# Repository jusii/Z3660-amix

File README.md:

# Z3660 by sHaNsHe (Double H Tech)

<!-- fork:amix begin — self-contained fork section, safe to drop on an upstream merge -->
> ## This fork — Amiga UNIX (AMIX) support
>
> This is an **Amix-interoperability fork** of [shanshe/Z3660](https://github.com/shanshe/Z3660)
> (GPL-3.0, full credit to sHaNsHe). It adds a **real 68030 PMMU emulator** and an **emulated
> A3000 mainboard SCSI** so a Z3660 + Z-turn can boot **Amiga UNIX (AMIX) 2.1**. If you don't run
> AMIX, nothing changes — the additions default to off and upstream behaviour is unchanged.
>
> **What's new in this fork** (full reference: **[docs/AMIX.md](docs/AMIX.md)**):
> - **68030 PMMU emulation** — new `bootmode UAE_030_MMU` (a 68030 interpreter *with* a working PMMU).
> - **Emulated A3000 SCSI** — AMIX's kernel bootstrap path (SuperDMAC + WD33C93).
> - **New config knobs** — `amix_mode` (AMIX memory contract) and `service_cadence` (emulator
>   throughput vs. interrupt latency), plus `DEMU`/`DSCSI` runtime debug gating and the
>   `perf_stats`/`emu_probes`/`core0_stats` run-loop overhead switches (all default to the
>   unchanged behaviour).
> - **Guest-side AMIX drivers** — the SCSI and ethernet drivers that run *inside* AMIX against the
>   protocol this firmware serves have their own repos:
>   **[amix-z3660scsi](https://github.com/jusii/amix-z3660scsi)** and
>   **[amix-z3660net](https://github.com/jusii/amix-z3660net)**. The kernel that carries them is
>   assembled with the shared build harness in
>   **[amix-kerntools](https://github.com/jusii/amix-kerntools)**.
>
> ### Quick start — try a pre-built firmware
> 1. Download `BOOT.BIN` from this repo's **Releases** (no build needed), or build it yourself —
>    see *Build it yourself* below.
> 2. Copy it to the SD card's FAT32 boot partition; use the layout in
>    [`z3660-zturn_SD_content/`](z3660-zturn_SD_content/) for the rest.
> 3. **You supply your own Kickstart ROM(s) and disk image** — Amiga OS ROMs and AMIX itself are
>    copyrighted and are not included.
>
> ### Build it yourself
> A dockerised toolchain builds the firmware and the Amiga-side drivers — see
> **[docker/README.md](docker/README.md)**. (Drivers build with no AMD account; the full firmware
> build needs you to download AMD/Xilinx Vitis 2023.2 yourself — it is staged outside the repo and
> never committed.)
>
> Three firmware images come out of the one tree. `make bootbin` gives the usual **`BOOT.BIN`**,
> with the emulator's run-loop diagnostics compiled in and switchable at runtime; `make lean` gives
> **`BOOT-lean.BIN`**, the production image with those diagnostics — and their per-instruction
> predicates — compiled out; and `make profile` gives **`BOOT-prof.BIN`**, the lean image plus an
> interpreter profiler (a wall-clock guest-PC sampler and per-stage ARM cycle attribution). The
> profiling image is a measuring instrument, not a production one — it costs measured time to run.
> Every build also drops a CRC-stamped copy of its image, plus the matching core1 emulator ELF,
> in `sd_card/archive/` (untracked), so a rebuild never destroys the image you are comparing
> against, and a flown image's disassembly stays readable after the build directory has moved on.
> Details in
> **[docs/AMIX.md](docs/AMIX.md)** and **[docs/profiler.md](docs/profiler.md)**.
>
> A fourth target, `make q2probe`, builds **`BOOT-q2probe.BIN`** — a throwaway experiment image
> that answers one open design question about generated code and prints its verdict on serial
> before emulation starts. It is compiled out of all three images above (their CRCs are
> unchanged whether it exists in the tree or not), and it is meant to be booted once, not left
> on a card. See **[docs/WARP-ENGINE.md](docs/WARP-ENGINE.md)**.
>
> ### Running AMIX
> Needs an **A3000-variant Kickstart** (A4000 ROMs can't boot AMIX) and an **AMIX disk image** placed
> on the **SCSI id it was installed on** (id 6 for the usual A3000 install — see the note in
> docs/AMIX.md). AMIX 2.1 **boots to a stable multiuser login shell**; full setup, the SCSI-id rule
> and current status are in **[docs/AMIX.md](docs/AMIX.md)**.
>
> ### Branches
> - **`amix-main-2` — the branch of record.** The Amix work rebuilt on upstream firmware
>   **v1.03 beta 21**. Upstream rewrote its history, so there was no merge base and the resync had
>   to be a guided replay rather than a merge;
>   **[docs/port-ledger-beta21.md](docs/port-ledger-beta21.md)** is the analysis behind it.
> - **`amix-main`** — the superseded pre-beta-21 line, kept for reference. It shares no ancestry
>   with `amix-main-2`. Documents dated before the resync describe that tree and say so.
>
> ### The fork's own documents
> - **[docs/AMIX.md](docs/AMIX.md)** — the AMIX reference: boot modes, the new config keys, how the
>   A3000-SCSI bootstrap works, current status, and the upstream defects this resync turned up.
> - **[KNOWN_ISSUES.md](KNOWN_ISSUES.md)** — limitations, including the fork note on the real-CPU
>   `cpufreq` ceiling being a per-card property.
> - **[CHANGELOG.md](CHANGELOG.md)** — this fork's history and its measurements. (Upstream's own
>   history is the separate **CHANGES.md**, which the text below points you at.)
> - **[docs/](docs/)** — the engineering references: clock timings, the piscsi service path, the
>   HTTP/TFTP deploy route, the WARP decoded-op-cache engine, the interpreter profiler.
<!-- fork:amix end -->

<br>Z3660 is an Amiga 4000 CPU accelerator board based on A3660 and Z-turn FPGA board.
<br>
<br>Compared to A3660, Z3660 has some key differences:
<br><p style="margin-left:1em;">
<br><b>1</b>. Z3660 accelerator board can only use 060 CPUs. This could be changed in the future, but at this time, only 060 is supported.
<br>
<br><b>2</b>. If Z-turn FPGA board is <b>NOT</b> used, then you get a simple A3660. The only difference is that all A3660 PLDs are replaced by a XC95144XL-10TQ144 CPLD. It could be possible to use 060 up to 100MHz, but only 50 MHz and 64 MHz has been tested. A board with 128 MB of CPU RAM is in the works (to be connected at Z-turn sockets).
<br>
<br><b>3</b>. If you <b>use a Z-turn FPGA board</b>, then you can add 128 MB of CPU RAM (DMA compatible), 256 MB of Z3 RAM (not DMA compatible), RTG 16bit, Ethernet, AHI and MHI. Also there is a SD to SCSI emulation for using raw RDB disk images (USB storage maybe in the future). And of course, you can use a 68060 rev6 at 100 MHz.
<br><p style="margin-left:0em;">
<br><b>Main branch. Z3660 with Z-turn FPGA</b>
<br>
<br>This main branch has everything you need to build a Z3660 with Z-turn FPGA.
<br>If you want to build Z3660 without Z-turn FPGA, please go to wo_FPGA branch. The board is the same, but the CPLD firmware and BOM are obviously different.
<br>
<br>Current version of Schematics is v021. It has all fixes needed by v02 to have DMA compatibility (tested with ReA4091 as bus master), so you can build it.
<br>
<br>The exact model of Z-Turn board you will need is: MYS-7Z020-V2 ( [mouser](https://www.mouser.com/c/?q=MYS-7Z020-V2-0E1D-766-C) (C or C-S. C-S has restrictions on EU - UK) ).

<br>
<br><p style="text-align:center;"><br>v0.2 Z3660 without FPGA</br></p>
<br>
<br><p style="text-align:center;"><br>v0.2 Z3660 with FPGA</br></p>
In this version you can see that I have used a 3V3 DCDC converter, instead of old linear regulator on VR1. Board has both footprints in one. Please be careful with its connection.
<br>
<br>Note on RTG status: RTG is full working now. It has all features that ZZ9000 has (except obviously scandoubler). Due limitations of Z-turn, output video is limited to 16 bit.
<br>Manufacturer ID was asigned to 5195 decimal, 0x144B hexadecimal (thanks to Olaf Barthel).
<br>All RTG, AHI and MHI are based on [ZZ9000 RTG](https://source.mnt.re/explore).
It has the same band-pass filters as the AX module, but made in software by one of the ARMs.
<br>
<br><b>And finally, a checkmate move...</b>
<br>
<br><i>Don't have a 060 rev6 CPU, and still want to try Z3660 with a Z-turn?</i>
<br><i>sHaNsHe to the rescue!!! :P</i>
<br>
<br>One of the Z-turn ARM CPU can run the emulation code of a 68040 CPU with JIT that reaches up to 120 MIPS!!!<br>It is based on Amiberry CPU code (for 32bit ARM). (And yes, I know, but Emu68 no longer supports 32 bit ARM).
<br>You can even switch between the real 060 CPU and the emulation by clicking on an app (and rebooting).
<br>
<br><b>Discord channel link:</b>
<br><br>https://discord.gg/ua4u6SzyHf
<br>
<br><b>Documents to read before using your Z3660</b><br>
<br> You should read the "KNOWN_ISSUES.md" and "CHANGES.md" files to know the latest news.
<br> Thanks to ByteMavericks we have now the [wiki](https://github.com/shanshe/Z3660/wiki)

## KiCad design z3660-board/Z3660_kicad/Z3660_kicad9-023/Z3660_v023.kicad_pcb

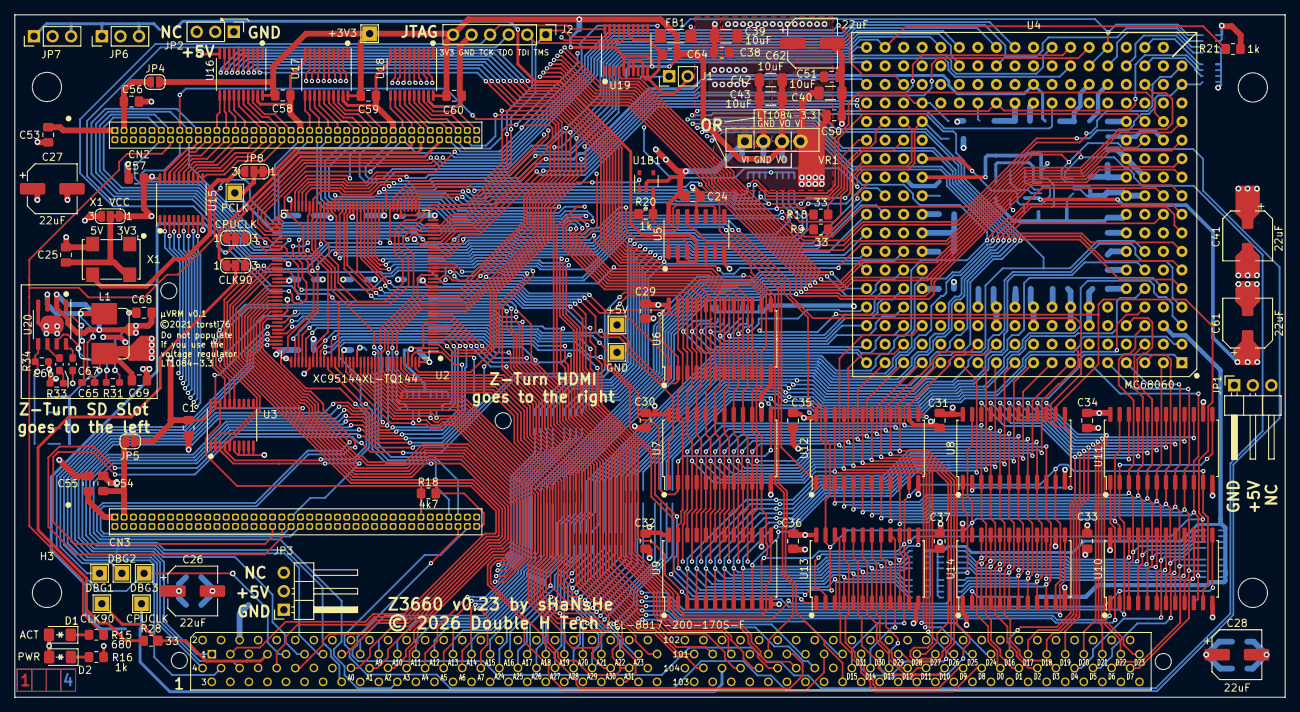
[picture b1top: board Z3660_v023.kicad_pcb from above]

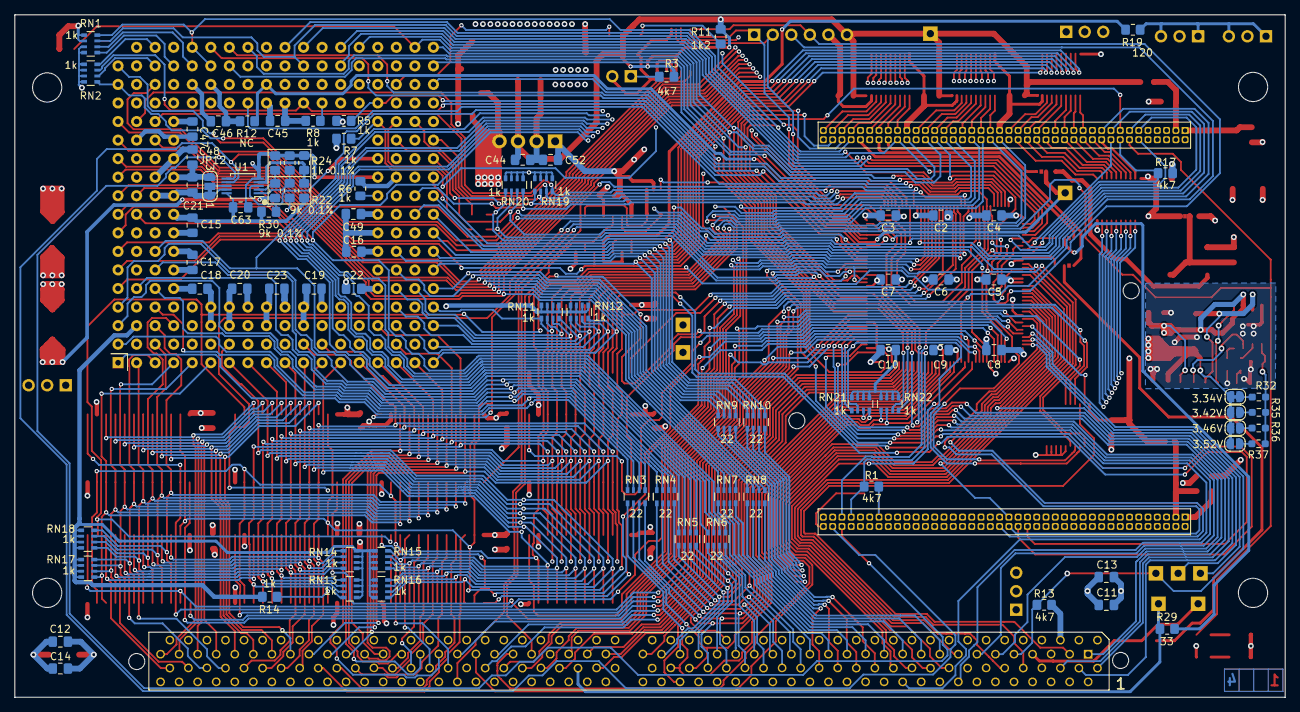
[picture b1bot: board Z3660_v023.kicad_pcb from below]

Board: 4 copper layers, 173.9 x 93.4 mm, 195 parts (87 on the bottom side), 321 nets.

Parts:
C1, C2, C3, C4, C5, C6, C7, C8, C9, C10, C11, C12, C13, C14, C15, C16, C17, C18, C19, C20, C21, C22, C23, C24, C25, C29, C30, C31, C32, C33, C34, C35, C36, C37, C38, C44, C45, C46, C47, C48, C49, C50, C51, C52, C53, C54, C55, C56, C57, C58, C59, C60, C63, C64: 100nF; C_0805_2012Metric_Pad1.18x1.45mm_HandSolder
C26, C28, C41, C61, C62: 22uF; CP_Elec_6.3x5.4
C27: 22uF; CP_Elec_6.3x3.9
C39, C40, C42, C43: 10uF; C_1206_3216Metric_Pad1.33x1.80mm_HandSolder
C65: 10nF; C_0603_1608Metric_Pad1.08x0.95mm_HandSolder
C66: 3.9nF; C_0603_1608Metric_Pad1.08x0.95mm_HandSolder
C67: 100nF; C_0603_1608Metric_Pad1.08x0.95mm_HandSolder
C68: 10uF; C_0805_2012Metric_Pad1.18x1.45mm_HandSolder
C69: 22uF; C_0805_2012Metric_Pad1.18x1.45mm_HandSolder
CN1: KEL-8817-200-170S-F; xIP-200
CN2: Conn_02x40_Odd_Even; PinHeader_2x40_P1.27mm_Vertical
CN3: Conn_02x40_Odd_Even; PinHeader_2x40_P1.27mm_Vertical_CN3
D1: LED_Small_Green; LED_1206_3216Metric_Pad1.42x1.75mm_HandSolder
D2: LED_Small_Red; LED_1206_3216Metric_Pad1.42x1.75mm_HandSolder
DBG1, DBG2, DBG3: PCLK; TestPoint_THTPad_2.0x2.0mm_Drill1.0mm
FB1: Ferrite_Bead_Small; Fuse_1806_4516Metric_Pad1.57x1.80mm_HandSolder
H1, H2, H3, H4: MountingHole; MountingHole_4mm
H5, H6, H7, H8: MountingHole; MountingHole_2.2mm_M2
J1: Jumper_2_Open; PinHeader_1x02_P2.54mm_Vertical
J2: JTAG; PinHeader_1x06_P2.54mm_Vertical
JP1, JP3: Jumper_NO_Small; PinHeader_1x03_P2.54mm_Horizontal
JP2, JP6, JP7: Jumper_3_Open; PinHeader_1x03_P2.54mm_Vertical
JP4, JP5: BRIDGE_3V3; SolderJumper-2_P1.3mm_Open_RoundedPad1.0x1.5mm
JP8, JP9, JP10, JP11, JP12: SolderJumper_3_Bridged12; SolderJumper-3_P1.3mm_Bridged12_RoundedPad1.0x1.5mm_NumberL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
JP13, JP14, JP15, JP16: SolderJumper_2_Open; small_SolderJumper-2_P1.3mm_Open_RoundedPad1.0x1.5mm
L1: 10uH; L_Bourns_SRP7028A_7.3x6.6mm
NT1, NT2, NT3, NT4: NetTie_2; NetTie-2_SMD_Pad0.5mm
R1, R3, R13, R17, R18: 4k7; R_0805_2012Metric_Pad1.20x1.40mm_HandSolder
R5, R6, R7, R8, R14, R16, R20, R21: 1k; R_0805_2012Metric_Pad1.20x1.40mm_HandSolder
R9, R10, R28, R29: 33; R_0805_2012Metric_Pad1.20x1.40mm_HandSolder
R11: 1k2; R_0805_2012Metric_Pad1.20x1.40mm_HandSolder
R12: NC; R_0805_2012Metric_Pad1.20x1.40mm_HandSolder
R15: 680; R_0805_2012Metric_Pad1.20x1.40mm_HandSolder
R19: 120; R_0805_2012Metric_Pad1.20x1.40mm_HandSolder
R22, R26, R27, R30: 9k 0.1%; R_0805_2012Metric_Pad1.20x1.40mm_HandSolder
R23, R24, R25: 1k 0.1%; R_0805_2012Metric_Pad1.20x1.40mm_HandSolder
R31: 100k; R_0603_1608Metric_Pad0.98x0.95mm_HandSolder
R32: 26.1k*; R_0603_1608Metric_Pad0.98x0.95mm_HandSolder
R33: 6.8k; R_0603_1608Metric_Pad0.98x0.95mm_HandSolder
R34: 10k; R_0603_1608Metric_Pad0.98x0.95mm_HandSolder
R35: 27.0k; R_0603_1608Metric_Pad0.98x0.95mm_HandSolder
R36: 27.4k; R_0603_1608Metric_Pad0.98x0.95mm_HandSolder
R37: 28.0k; R_0603_1608Metric_Pad0.98x0.95mm_HandSolder
RN1, RN2, RN11, RN12, RN13, RN14, RN15, RN16, RN17, RN18, RN19, RN20, RN21, RN22: 1k; R_Array_Convex_4x0603
RN3, RN4, RN5, RN6, RN7, RN8, RN9, RN10: 22; R_Array_Convex_4x0603
TP1: +3V3; TestPoint_THTPad_2.0x2.0mm_Drill1.0mm
TP4: +5V; TestPoint_THTPad_2.0x2.0mm_Drill1.0mm
TP8: GND; TestPoint_THTPad_2.0x2.0mm_Drill1.0mm
TP9: PCLK; TestPoint_THTPad_2.0x2.0mm_Drill1.0mm
TP10: CLK90; TestPoint_THTPad_2.0x2.0mm_Drill1.0mm
TP11: CPUCLK; TestPoint_THTPad_2.0x2.0mm_Drill1.0mm
U1: LTC2990; MSOP-10_3x3mm_P0.5mm
U1B1: BU4942; TSOP-5_1.65x3.05mm_P0.95mm
U2: XC95144XL-TQ144; TQFP-144_20x20mm_P0.5mm
U3, U15, U16, U17, U18: SN74CB3T3245PW; TSSOP-20_4.4x6.5mm_P0.65mm
U4: MC68060; PGA226
U5: 7407; SOIC-14_3.9x8.7mm_P1.27mm
U6, U7, U8, U9, U10, U11, U12, U13, U14: 74FCT543A; SOIC-24W_7.5x15.4mm_P1.27mm
U19: PCF8574TS; TSSOP-20_4.4x6.5mm_P0.65mm
U20: MP2307; SOIC-8-1EP_3.9x4.9mm_P1.27mm_EP2.514x3.2mm
VR1: LT1084-3.3_EXTENDED; Regulador_DCDC
X1: IQXO-70; Oscillator_SMD_IQD_IQXO70-4Pin_7.5x5.0mm

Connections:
3.3V_ZTURN1: C54.1, CN3.3, JP5.1 (A)
3.3V_ZTURN2: C56.1, CN2.3, JP4.1 (A)
040A0: RN10.4 (R4.1), RN22.6 (R3.2), U2.121
040A1: RN10.3 (R3.1), RN22.5 (R4.2), U2.124
040A2: RN10.2 (R2.1), RN21.8 (R1.2), U2.125
040A3: RN10.1 (R1.1), RN21.7 (R2.2), U2.126
040A4: CN1.52 (A4), RN9.4 (R4.1)
040A5: CN1.56 (A5), RN9.3 (R3.1)
040A6: CN1.60 (A6), RN9.2 (R2.1)
040A7: CN1.64 (A7), RN9.1 (R1.1)
040A8: CN1.33 (A8), RN8.4 (R4.1)
040A9: CN1.37 (A9), RN8.3 (R3.1)
040A10: CN1.41 (A10), RN8.2 (R2.1)
040A11: CN1.45 (A11), RN8.1 (R1.1)
040A12: CN1.49 (A12), RN7.4 (R4.1)
040A13: CN1.53 (A13), RN7.3 (R3.1)
040A14: CN1.57 (A14), RN7.2 (R2.1)
040A15: CN1.61 (A15), RN7.1 (R1.1)
040A16: CN1.65 (A16), RN6.4 (R4.1)
040A17: CN1.69 (A17), RN6.3 (R3.1)
040A18: CN1.73 (A18), RN6.2 (R2.1)
040A19: CN1.77 (A19), RN6.1 (R1.1), U2.140
040A20: CN1.81 (A20), RN5.4 (R4.1), U2.139
040A21: CN1.85 (A21), RN5.3 (R3.1), U2.138
040A22: CN1.89 (A22), RN5.2 (R2.1), U2.137
040A23: CN1.93 (A23), RN5.1 (R1.1), U2.136
040A24: CN1.68 (MA24), RN4.4 (R4.1), U2.135
040A25: CN1.72 (MA25), RN4.3 (R3.1), U2.134
040A26: CN1.76 (MA26), RN4.2 (R2.1), U2.133
040A27: CN1.80 (A27), RN4.1 (R1.1), U2.132
040A28: CN1.84 (A28), RN3.4 (R4.1), U2.131
040A29: CN1.88 (A29), RN3.3 (R3.1), U2.130
040A30: CN1.92 (A30), RN3.2 (R2.1), U2.129
040A31: CN1.96 (A31), RN3.1 (R1.1), U2.128
060A0: RN10.5 (R4.2), U4.102 (A0), U16.9 (A7)
060A1: RN10.6 (R3.2), U4.96 (A1), U16.8 (A6)
060A2: RN10.7 (R2.2), U4.89 (A2), U16.7 (A5)
060A3: RN10.8 (R1.2), U4.90 (A3), U16.6 (A4)
060A4: RN9.5 (R4.2), U4.84 (A4), U16.5 (A3)
060A5: RN9.6 (R3.2), U4.78 (A5), U16.4 (A2)
060A6: RN9.7 (R2.2), U4.76 (A6), U16.3 (A1)
060A7: RN9.8 (R1.2), U4.72 (A7), U16.2 (A0)
060A8: RN8.5 (R4.2), U4.66 (A8), U17.9 (A7)
060A9: RN8.6 (R3.2), U4.70 (A9), U17.8 (A6)
060A10: RN8.7 (R2.2), U4.115 (A10), U17.7 (A5)
060A11: RN8.8 (R1.2), U4.111 (A11), U17.6 (A4)
060A12: RN7.5 (R4.2), U4.109 (A12), U17.5 (A3)
060A13: RN7.6 (R3.2), U4.103 (A13), U17.4 (A2)
060A14: RN7.7 (R2.2), U4.97 (A14), U17.3 (A1)
060A15: RN7.8 (R1.2), U4.91 (A15), U17.2 (A0)
060A16: RN6.5 (R4.2), U4.92 (A16), U18.9 (A7)
060A17: RN6.6 (R3.2), U4.85 (A17), U18.8 (A6)
060A18: RN6.7 (R2.2), U4.79 (A18), U18.7 (A5)
060A19: RN6.8 (R1.2), U4.86 (A19), U18.6 (A4)
060A20: RN5.5 (R4.2), U4.73 (A20), U18.5 (A3)
060A21: RN5.6 (R3.2), U4.67 (A21), U18.4 (A2)
060A22: RN5.7 (R2.2), U4.61 (A22), U18.3 (A1)
060A23: RN5.8 (R1.2), U4.75 (A23), U18.2 (A0)
060A24: RN4.5 (R4.2), U4.55 (A24), U15.2 (A0)
060A25: RN4.6 (R3.2), U4.69 (A25), U15.3 (A1)
060A26: RN4.7 (R2.2), U4.62 (A26), U15.4 (A2)
060A27: RN4.8 (R1.2), U4.37 (A27), U15.5 (A3)
060A28: RN3.5 (R4.2), U4.63 (A28), U15.6 (A4)
060A29: RN3.6 (R3.2), U4.19 (A29), U15.7 (A5)
060A30: RN3.7 (R2.2), U4.57 (A30), U15.8 (A6)
060A31: RN3.8 (R1.2), U4.1 (A31), U15.9 (A7)
+3.3VADC: NT2.2, R22.2, R30.2
+3V3: C1.1, C2.1, C3.1, C4.1, C5.1, C6.1, C7.1, C8.1, C9.1, C10.1, C15.1, C16.1, C17.1, C18.1, C19.1, C20.1, C21.1, C22.1, C23.1, C41.1, C42.1, C43.1, C44.1, C45.1, C46.1, C47.1, C48.1, C49.1, C57.1, C58.1, C59.1, C60.1, C63.1, C64.1, C69.1, J2.6, JP4.2 (B), JP5.2 (B), JP11.1 (A), JP12.3 (B), JP13.1 (A), JP14.1 (A), JP15.1 (A), JP16.1 (A), L1.1, NT2.1, NT4.1, R3.2, R5.1, R6.1, R7.1, R8.1, R11.2, R14.1, R21.2, R27.2, RN1.1 (R1.1), RN1.2 (R2.1), RN11.1 (R1.1), RN11.2 (R2.1), RN11.3 (R3.1), RN11.4 (R4.1), RN12.1 (R1.1), RN12.2 (R2.1), RN12.3 (R3.1), RN12.4 (R4.1), RN13.1 (R1.1), RN13.2 (R2.1), RN13.3 (R3.1), RN13.4 (R4.1), RN14.1 (R1.1), RN14.2 (R2.1), RN14.3 (R3.1), RN14.4 (R4.1), RN15.1 (R1.1), RN15.2 (R2.1), RN15.3 (R3.1), RN15.4 (R4.1), RN16.1 (R1.1), RN16.2 (R2.1), RN16.3 (R3.1), RN16.4 (R4.1), RN17.1 (R1.1), RN17.2 (R2.1), RN17.3 (R3.1), RN17.4 (R4.1), RN18.1 (R1.1), RN18.2 (R2.1), RN18.3 (R3.1), RN18.4 (R4.1), RN19.1 (R1.1), RN19.2 (R2.1), RN19.3 (R3.1), RN19.4 (R4.1), RN20.1 (R1.1), RN20.2 (R2.1), RN20.3 (R3.1), RN20.4 (R4.1), RN21.1 (R1.1), RN21.2 (R2.1), RN21.3 (R3.1), RN21.4 (R4.1), RN22.1 (R1.1), RN22.2 (R2.1), RN22.3 (R3.1), RN22.4 (R4.1), TP1.1, U1.10 (VCC), U2.1 (VCCIO), U2.8 (VCCINT), U2.37 (VCCIO), U2.42 (VCCINT), U2.55 (VCCIO), U2.73 (VCCIO), U2.84 (VCCINT), U2.109 (VCCIO), U2.127 (VCCIO), U2.141 (VCCINT), U3.20 (VCC), U4.23 (VCC11), U4.27 (VCC12), U4.32 (VCC13), U4.38 (VCC14), U4.41 (VCC23), U4.44 (VCC24), U4.46 (VCC25), U4.48 (VCC26), U4.50 (VCC2), U4.53 (VCC15), U4.74 (VCC16), U4.77 (VCC17), U4.81 (VCC3), U4.82 (VCC4), U4.87 (VCC5), U4.88 (VCC6), U4.100 (VCC7), U4.104 (VCC18), U4.105 (VCC9), U4.107 (VCC19), U4.128 (VCC20), U4.131 (VCC8), U4.134 (VCC0), U4.138 (VCC10), U4.143 (VCC21), U4.152 (VCC1), U4.160 (VCC22), U4.180 (VCC0), U4.181 (VCC0), U4.182 (VCC0), U4.183 (VCC0), U4.184 (VCC0), U4.185 (VCC0), U4.188 (VCC0), U4.189 (VCC0), U4.192 (VCC0), U4.193 (VCC0), U4.195 (VCC0), U4.198 (VCC0), U4.199 (VCC0), U4.207 (VCC0), U15.20 (VCC), U16.20 (VCC), U17.20 (VCC), U18.20 (VCC), U19.5 (VDD), VR1.3 (VO)
+5V: C11.1, C12.1, C13.1, C14.1, C24.1, C26.1, C27.1, C28.1, C29.1, C30.1, C31.1, C32.1, C33.1, C34.1, C35.1, C36.1, C37.1, C38.1, C39.1, C40.1, C50.1, C51.1, C52.1, C53.1, C55.1, C61.1, C62.1, C68.1, CN1.14 (+5V), CN1.15 (+5V), CN1.18 (+5V), CN1.19 (+5V), CN1.22 (+5V), CN1.23 (+5V), CN1.26 (+5V), CN1.27 (+5V), CN1.94 (+5V), CN1.95 (+5V), CN1.98 (+5V), CN1.99 (+5V), CN1.102 (+5V), CN1.103 (+5V), CN1.106 (+5V), CN1.107 (+5V), CN1.174 (+5V), CN1.175 (+5V), CN1.178 (+5V), CN1.179 (+5V), CN1.182 (+5V), CN1.183 (+5V), CN1.186 (+5V), CN1.187 (+5V), CN2.1, CN3.1, D1.2 (A), D2.2 (A), JP1.2, JP2.2, JP3.2, JP6.2 (C), JP7.2 (C), JP11.3 (B), R26.2, R31.2, TP4.1, U1B1.2 (VDD), U5.14 (VCC), U6.24 (VCC), U7.24 (VCC), U8.24 (VCC), U9.24 (VCC), U10.24 (VCC), U11.24 (VCC), U12.24 (VCC), U13.24 (VCC), U14.24 (VCC), U20.2 (VIN), VR1.1 (VI), VR1.4 (VI)
/CPU and CLK/SIZ60_0: R10.1, U4.119 (SIZ0)
/CPU and CLK/SIZ60_1: R9.1, U4.118 (SIZ1)
/ZTURN and 3.3V/BP: CN3.80, R18.2
A0: CN1.36 (A0), U2.88
A1: CN1.40 (A1), U2.91
A2: CN1.44 (A2), U2.92
A3: CN1.48 (A3), U2.93
BCLK_FPGA: CN3.39, U2.95
CLK90: CN1.13 (CLK90), R28.2, TP10.1
CLK90_CPLD: JP9.3 (B), U2.83
CLK90_FPGA: CN2.68, JP9.1 (A)
CPUCLK: CN1.112 (CPUCLK), R29.2, TP11.1
CPUCLK_CPLD: JP10.3 (B), U2.79
CPUCLK_FPGA: CN2.72, JP10.1 (A)
CPUCLK_RECVD: CN1.135 (CPUCLKB_RECVD), U2.46
D0: CN1.172 (D0), U10.22 (B0), U14.22 (B0)
D1: CN1.176 (D1), U10.21 (B1), U14.21 (B1)
D2: CN1.180 (D2), U10.20 (B2), U14.20 (B2)
D3: CN1.184 (D3), U10.19 (B3), U14.19 (B3)
D4: CN1.188 (D4), U10.18 (B4), U14.18 (B4)
D5: CN1.192 (D5), U10.17 (B5), U14.17 (B5)
D6: CN1.196 (D6), U10.16 (B6), U14.16 (B6)
D7: CN1.200 (D7), U10.15 (B7), U14.15 (B7)
D8: CN1.168 (D8), U13.22 (B0)
D9: CN1.164 (D9), U13.21 (B1)
D10: CN1.160 (D10), U13.20 (B2)
D11: CN1.156 (D11), U13.19 (B3)
D12: CN1.152 (D12), U13.18 (B4)
D13: CN1.148 (D13), U13.17 (B5)
D14: CN1.144 (D14), U13.16 (B6)
D15: CN1.140 (D15), U13.15 (B7)
D16: CN1.169 (D16), U8.22 (B0), U11.22 (B0)
D17: CN1.173 (D17), U8.21 (B1), U11.21 (B1)
D18: CN1.177 (D18), U8.20 (B2), U11.20 (B2)
D19: CN1.181 (D19), U8.19 (B3), U11.19 (B3)
D20: CN1.185 (D20), U8.18 (B4), U11.18 (B4)
D21: CN1.189 (D21), U8.17 (B5), U11.17 (B5)
D22: CN1.193 (D22), U8.16 (B6), U11.16 (B6)
D23: CN1.197 (D23), U8.15 (B7), U11.15 (B7)
D24: CN1.165 (D24), U6.22 (B0), U7.22 (B0), U9.22 (B0), U12.22 (B0)
D25: CN1.161 (D25), U6.21 (B1), U7.21 (B1), U9.21 (B1), U12.21 (B1)
D26: CN1.157 (D26), U6.20 (B2), U7.20 (B2), U9.20 (B2), U12.20 (B2)
D27: CN1.153 (D27), U6.19 (B3), U7.19 (B3), U9.19 (B3), U12.19 (B3)
D28: CN1.149 (D28), U6.18 (B4), U7.18 (B4), U9.18 (B4), U12.18 (B4)
D29: CN1.145 (D29), U6.17 (B5), U7.17 (B5), U9.17 (B5), U12.17 (B5)
D30: CN1.141 (D30), U6.16 (B6), U7.16 (B6), U9.16 (B6), U12.16 (B6)
D31: CN1.137 (D31), U6.15 (B7), U7.15 (B7), U9.15 (B7), U12.15 (B7)
D040_0: CN3.7, RN18.8 (R1.2), U4.39 (D0), U10.3 (A0), U11.3 (A0), U12.3 (A0)
D040_1: CN3.9, RN18.7 (R2.2), U4.21 (D1), U10.4 (A1), U11.4 (A1), U12.4 (A1)
D040_2: CN3.11, RN18.6 (R3.2), U4.40 (D2), U10.5 (A2), U11.5 (A2), U12.5 (A2)
D040_3: CN3.13, RN18.5 (R4.2), U4.2 (D3), U10.6 (A3), U11.6 (A3), U12.6 (A3)
D040_4: CN3.17, RN17.8 (R1.2), U4.3 (D4), U10.7 (A4), U11.7 (A4), U12.7 (A4)
D040_5: CN3.19, RN17.7 (R2.2), U4.4 (D5), U10.8 (A5), U11.8 (A5), U12.8 (A5)
D040_6: CN3.21, RN17.6 (R3.2), U4.5 (D6), U10.9 (A6), U11.9 (A6), U12.9 (A6)
D040_7: CN3.23, RN17.5 (R4.2), U4.6 (D7), U10.10 (A7), U11.10 (A7), U12.10 (A7)
D040_8: CN3.27, RN16.5 (R4.2), U4.25 (D8), U9.3 (A0), U13.3 (A0)
D040_9: CN3.29, RN16.6 (R3.2), U4.7 (D9), U9.4 (A1), U13.4 (A1)
D040_10: CN3.31, RN16.7 (R2.2), U4.8 (D10), U9.5 (A2), U13.5 (A2)
D040_11: CN3.33, RN16.8 (R1.2), U4.9 (D11), U9.6 (A3), U13.6 (A3)
D040_12: CN3.37, RN15.5 (R4.2), U4.10 (D12), U9.7 (A4), U13.7 (A4)
D040_13: CN3.41, RN15.6 (R3.2), U4.11 (D13), U9.8 (A5), U13.8 (A5)
D040_14: CN3.43, RN15.7 (R2.2), U4.12 (D14), U9.9 (A6), U13.9 (A6)
D040_15: CN3.47, RN15.8 (R1.2), U4.13 (D15), U9.10 (A7), U13.10 (A7)
D040_16: CN3.16, RN14.5 (R4.2), U4.29 (D16), U7.3 (A0), U8.3 (A0), U14.3 (A0)
D040_17: CN3.18, RN14.6 (R3.2), U4.14 (D17), U7.4 (A1), U8.4 (A1), U14.4 (A1)
D040_18: CN3.20, RN14.7 (R2.2), U4.30 (D18), U7.5 (A2), U8.5 (A2), U14.5 (A2)
D040_19: CN3.22, RN14.8 (R1.2), U4.15 (D19), U7.6 (A3), U8.6 (A3), U14.6 (A3)
D040_20: CN3.26, RN13.5 (R4.2), U4.16 (D20), U7.7 (A4), U8.7 (A4), U14.7 (A4)
D040_21: CN3.28, RN13.6 (R3.2), U4.17 (D21), U7.8 (A5), U8.8 (A5), U14.8 (A5)
D040_22: CN3.30, RN13.7 (R2.2), U4.34 (D22), U7.9 (A6), U8.9 (A6), U14.9 (A6)
D040_23: CN3.32, RN13.8 (R1.2), U4.51 (D23), U7.10 (A7), U8.10 (A7), U14.10 (A7)
D040_24: CN3.36, RN12.8 (R1.2), U4.18 (D24), U6.3 (A0)
D040_25: CN3.38, RN12.7 (R2.2), U4.52 (D25), U6.4 (A1)
D040_26: CN2.52, RN12.6 (R3.2), U4.36 (D26), U6.5 (A2)
D040_27: CN2.54, RN12.5 (R4.2), U4.58 (D27), U6.6 (A3)
D040_28: CN2.42, RN11.8 (R1.2), U4.54 (D28), U6.7 (A4)
D040_29: CN2.44, RN11.7 (R2.2), U4.64 (D29), U6.8 (A5)
D040_30: CN2.46, RN11.6 (R3.2), U4.65 (D30), U6.9 (A6)
D040_31: CN2.48, RN11.5 (R4.2), U4.60 (D31), U6.10 (A7)
Earth: C1.2, C2.2, C3.2, C4.2, C5.2, C6.2, C7.2, C8.2, C9.2, C10.2, C11.2, C12.2, C13.2, C14.2, C15.2, C16.2, C17.2, C18.2, C19.2, C20.2, C21.2, C22.2, C23.2, C24.2, C25.2, C26.2, C27.2, C28.2, C29.2, C30.2, C31.2, C32.2, C33.2, C34.2, C35.2, C36.2, C37.2, C38.2, C39.2, C40.2, C41.2, C42.2, C43.2, C44.2, C45.2, C46.2, C47.2, C48.2, C49.2, C50.2, C51.2, C52.2, C53.2, C54.2, C55.2, C56.2, C57.2, C58.2, C59.2, C60.2, C61.2, C62.2, C63.2, C64.2, C67.1, C68.2, C69.2, CN1.2 (GND), CN1.3 (GND), CN1.6 (GND), CN1.7 (GND), CN1.10 (GND), CN1.11 (GND), CN1.35 (GND), CN1.38 (GND), CN1.39 (GND), CN1.47 (GND), CN1.50 (GND), CN1.51 (GND), CN1.59 (GND), CN1.62 (GND), CN1.63 (GND), CN1.71 (GND), CN1.74 (GND), CN1.75 (GND), CN1.83 (GND), CN1.86 (GND), CN1.87 (GND), CN1.115 (GND), CN1.118 (GND), CN1.119 (GND), CN1.127 (GND), CN1.130 (GND), CN1.131 (GND), CN1.138 (GND), CN1.139 (GND), CN1.142 (GND), CN1.143 (GND), CN1.151 (GND), CN1.154 (GND), CN1.155 (GND), CN1.163 (GND), CN1.166 (GND), CN1.167 (GND), CN1.190 (GND), CN1.191 (GND), CN1.194 (GND), CN1.195 (GND), CN1.198 (GND), CN1.199 (GND), CN2.2, CN2.4, CN2.20, CN2.21, CN2.30, CN2.31, CN2.40, CN2.41, CN2.50, CN2.60, CN2.61, CN2.70, CN2.71, CN2.80, CN3.2, CN3.4, CN3.24, CN3.25, CN3.34, CN3.35, CN3.44, CN3.54, CN3.67, CN3.68, J1.2 (B), J2.5, JP1.1, JP2.1, JP3.1, JP12.1 (A), NT1.2, R1.2, R12.2, R13.2, R16.1, R17.1, R18.1, R20.2, R33.2, R34.2, RN1.3 (R3.1), RN1.4 (R4.1), RN2.1 (R1.1), RN2.2 (R2.1), RN2.3 (R3.1), RN2.4 (R4.1), TP8.1, U1.5 (GND), U1.9 (ADR1), U1B1.3 (GND), U2.18 (GND), U2.29 (GND), U2.36 (GND), U2.47 (GND), U2.62 (GND), U2.72 (GND), U2.89 (GND), U2.90 (GND), U2.99 (GND), U2.108 (GND), U2.114 (GND), U2.123 (GND), U2.144 (GND), U3.6 (A4), U3.7 (A5), U3.8 (A6), U3.9 (A7), U3.10 (GND), U4.20 (GND17), U4.22 (GND18), U4.24 (GND19), U4.26 (GND20), U4.28 (GND21), U4.31 (GND22), U4.33 (GND23), U4.35 (GND24), U4.42 (GND3), U4.43 (GND4), U4.45 (GND5), U4.47 (GND6), U4.49 (GND7), U4.56 (GND25), U4.59 (GND26), U4.68 (GND27), U4.71 (GND28), U4.80 (GND29), U4.83 (GND30), U4.93 (GND8), U4.94 (GND9), U4.98 (GND31), U4.99 (GND10), U4.101 (GND32), U4.106 (GND11), U4.110 (GND33), U4.113 (GND34), U4.122 (GND35), U4.125 (GND36), U4.130 (GND12), U4.132 (GND1), U4.136 (GND2), U4.137 (GND13), U4.139 (GND14), U4.146 (GND37), U4.153 (GND0), U4.154 (GND15), U4.159 (GND38), U4.161 (GND39), U4.165 (GND16), U4.170 (DLE), U4.186 (GND3), U4.187 (GND2), U4.190 (GND1), U4.191 (GND0), U4.206 (GND0), U5.7 (GND), U5.9, U5.11, U6.12 (GND), U7.12 (GND), U7.14 (LEAB), U8.12 (GND), U9.12 (GND), U9.14 (LEAB), U10.12 (GND), U11.12 (GND), U11.14 (LEAB), U12.12 (GND), U12.14 (LEAB), U13.12 (GND), U14.1 (LEBA), U14.12 (GND), U14.14 (LEAB), U15.10 (GND), U15.19 (~OE), U16.10 (GND), U16.19 (~OE), U17.10 (GND), U17.19 (~OE), U18.10 (GND), U18.19 (~OE), U19.6 (A0), U19.7 (A1), U19.9 (A2), U19.15 (VSS), U20.4 (GND), U20.9 (GND), VR1.2 (GND), X1.2 (GND)
FC0: CN1.20 (FC0), U2.85
FC1: CN1.24 (FC1), U2.86
FC2: CN1.125 (FC2), U2.87
FPGA_PRESENCE: CN2.16, R17.2, U2.82
GNDA: NT1.1, NT3.1, R23.1, R24.1, R25.1
I2C0_CLK: CN3.78, U1.7 (SCL), U19.2 (SCL)
I2C0_SDA: CN3.76, U1.6 (SDA), U19.4 (SDA)
INT6_ARM: CN3.73, R1.1, U2.21
LEBUS0: U2.52, U6.1 (LEBA)
LEBUS1: U2.53, U7.1 (LEBA)
LEBUS2: U2.54, U8.1 (LEBA)
LEBUS3: U2.56, U9.1 (LEBA)
LEBUS4: U2.57, U13.1 (LEBA)
LEBUS5: U2.58, U12.1 (LEBA)
LEBUS6: U2.59, U11.1 (LEBA)
LEBUS7: U2.60, U10.1 (LEBA)
LEBUS_DMA: U2.34, U6.14 (LEAB), U8.14 (LEAB), U10.14 (LEAB), U13.14 (LEAB)
LED: CN2.14, R15.1, U5.1, U5.3
LEDR: JP6.1 (A), JP6.3 (B), JP7.1 (A), JP7.3 (B), R19.2
unnamed: C66.1, R33.1
unnamed: CN2.22, U15.18 (B0)
unnamed: CN2.23, U16.11 (B7)
unnamed: CN2.24, U15.17 (B1)
unnamed: CN2.25, U16.12 (B6)
unnamed: CN2.26, U15.16 (B2)
unnamed: CN2.27, U16.13 (B5)
unnamed: CN2.28, U15.15 (B3)
unnamed: CN2.29, U16.14 (B4)
unnamed: CN2.32, U15.14 (B4)
unnamed: CN2.33, U16.15 (B3)
unnamed: CN2.34, U15.13 (B5)
unnamed: CN2.35, U16.16 (B2)
unnamed: CN2.36, U15.12 (B6)
unnamed: CN2.37, U16.17 (B1)
unnamed: CN2.38, U15.11 (B7)
unnamed: CN2.39, U16.18 (B0)
unnamed: CN2.43, U17.11 (B7)
unnamed: CN2.45, U17.12 (B6)
unnamed: CN2.47, U17.13 (B5)
unnamed: CN2.49, U17.14 (B4)
unnamed: CN2.53, U17.15 (B3)
unnamed: CN2.55, U17.16 (B2)
unnamed: CN2.57, U17.17 (B1)
unnamed: CN2.59, U17.18 (B0)
unnamed: CN2.63, U18.11 (B7)
unnamed: CN2.65, U18.12 (B6)
unnamed: CN2.67, U18.13 (B5)
unnamed: CN2.69, U18.14 (B4)
unnamed: CN2.73, U18.15 (B3)
unnamed: CN2.75, U18.16 (B2)
unnamed: CN2.77, U18.17 (B1)
unnamed: CN2.79, U18.18 (B0)
unnamed: D1.1 (K), R15.2
unnamed: D2.1 (K), R16.2
unnamed: J1.1 (A), R3.1, U2.44
unnamed: JP9.2 (C), R28.1
unnamed: JP10.2 (C), R29.1
unnamed: C25.1, JP11.2 (C), X1.4 (V+)
unnamed: JP12.2 (C), U1.8 (ADR0)
unnamed: JP13.2 (B), NT4.2, R32.2
unnamed: JP14.2 (B), R35.2
unnamed: JP15.2 (B), R36.2
unnamed: JP16.2 (B), R37.2
unnamed: R19.1, U5.2, U5.4
unnamed: RN1.6 (R3.2), U4.149 (TMS)
unnamed: RN1.5 (R4.2), U4.148 (TCK)
unnamed: RN2.8 (R1.2), U4.164 (~TRST)
unnamed: RN2.6 (R3.2), U4.147 (TDI)
unnamed: R23.2, R27.1, U1.1 (V1)
unnamed: R25.2, R26.1, U1.2 (V2)
unnamed: R22.1, R24.2, U1.4 (V4)
unnamed: DBG1.1, U2.106
unnamed: DBG2.1, U2.107
unnamed: FB1.2, U4.142 (~TS)
unnamed: C65.1, U20.1 (BS)
unnamed: C66.2, U20.6 (COMP)
unnamed: R31.1, U20.7 (EN)
unnamed: R32.1, R34.1, R35.1, R36.1, R37.1, U20.5 (FB)
unnamed: C67.2, U20.8 (SS)
unnamed: C65.2, L1.2, U20.3 (SW)
OEBUS0: U2.104, U6.2 (_OEBA), U6.13 (_OEAB)
OEBUS1: U2.110, U7.2 (_OEBA), U7.13 (_OEAB)
OEBUS2: U2.111, U8.2 (_OEBA), U8.13 (_OEAB)
OEBUS3: U2.112, U9.2 (_OEBA), U9.13 (_OEAB)
OEBUS4: U2.113, U13.2 (_OEBA), U13.13 (_OEAB)
OEBUS5: U2.61, U12.2 (_OEBA), U12.13 (_OEAB)
OEBUS6: U2.116, U11.2 (_OEBA), U11.13 (_OEAB)
OEBUS7: U2.120, U10.2 (_OEBA), U10.13 (_OEAB)
PCLK: JP8.2 (C), R12.1, TP9.1, U2.30 (I/O/GCK1), U4.135 (PCLK)
PCLK_FPGA: CN2.66, JP8.1 (A)
PCLK_OSC: JP8.3 (B), X1.3 (OUT)
PS_MIO0: CN2.11, U2.78
PS_MIO8: CN2.13, U2.115
PS_MIO9: CN2.15, U2.20
PS_MIO12: CN2.17, U2.64
PS_MIO13: CN2.19, U2.48
PS_MIO15: CN2.18, U2.81
PUP_4: R14.2, U14.2 (_OEBA)
RESETOUT: R20.1, U2.27, U5.13
R_W: CN1.5 (R_W), U3.18 (B0)
R_W040: CN2.56, RN20.7 (R2.2), U2.19, U3.2 (A0), U4.112 (R_W)
SIZ0: CN1.121 (SIZ0), U2.97
SIZ1: CN1.129 (SIZ1), U2.96
SIZ40_0: CN2.76, R10.2, RN20.5 (R4.2), U2.14
SIZ40_1: CN2.78, R9.2, RN20.6 (R3.2), U2.15
TCK: J2.4, U2.67 (TCK), U19.20 (P7)
TDI: J2.2, U2.63 (TDI), U19.16 (P4)
TDO: J2.3, U2.122 (TDO), U19.17 (P5)
THERM_N: NT3.2, U4.196 (THERM0)
THERM_P: R30.1, U1.3 (V3), U4.197 (THERM1)
TM0: RN19.6 (R3.2), U2.40, U4.114 (TM0)
TM1: RN19.5 (R4.2), U2.39, U4.108 (TM1)
TM2: RN20.8 (R1.2), U2.38 (I/O/GCK3), U4.95 (TM2)
TMS: J2.1, U2.65 (TMS), U19.19 (P6)
TT0: RN19.7 (R2.2), U2.41, U4.117 (TT0)
TT1: RN19.8 (R1.2), U2.43, U4.116 (TT1)
V_DETECTOR: U1B1.1 (~RESET), U2.143 (I/O/GSR)
_040CIOUT: RN2.5 (R4.2), U2.45, U3.4 (A2), U4.127 (~CIOUT)
_040EMUL: RN1.8 (R1.2), U2.71, U4.150 (~MDIS), U4.166 (~CDIS)
_040IPEND: U3.5 (A3), U4.145 (~IPEND)
_040RSTI: CN2.12, U2.32 (I/O/GCK2), U4.151 (~RSTI)
_040RSTO: U2.25, U4.129 (~RST0), U5.5
_060IPL0: U2.70, U4.169 (IPL0)
_060IPL1: U2.69, U4.168 (IPL1)
_060IPL2: U2.68, U4.167 (IPL2)
_AS: CN1.133 (_AS), U2.117
_AVEC: CN1.12 (_AVEC), U2.16
_AVEC040: U2.76, U4.172 (~AVEC)
_BB040: R21.1, U2.17, U4.178 (~BB)
_BERR: CN1.29 (_BERR), U2.119
_BG: CN1.105 (_BG), U2.101
_BG040: U2.77, U4.174 (~BG)
_BGACK: CN1.8 (_BGACK), U2.94
_BGACK040: U2.102, U3.19 (~OE)
_BGR040: RN2.7 (R2.2), U2.28, U4.208 (~BGR)
_BOSS: CN1.17 (_BOSS), DBG3.1, R13.1, U2.105
_BR: CN1.25 (_BR), U2.6 (I/O/GTS2)
_BR040: U2.11, U4.179 (~BR)
_BTT: R5.2, U2.26, U4.212 (~BTT)
_CEAB: U2.23, U6.11 (_CEAB), U7.11 (_CEAB), U8.11 (_CEAB), U9.11 (_CEAB), U10.11 (_CEAB), U11.11 (_CEAB), U12.11 (_CEAB), U13.11 (_CEAB), U14.11 (_CEAB)
_CEBA: U2.80, U6.23 (_CEBA), U7.23 (_CEBA), U8.23 (_CEBA), U9.23 (_CEBA), U10.23 (_CEBA), U11.23 (_CEBA), U12.23 (_CEBA), U13.23 (_CEBA), U14.23 (_CEBA)
_CIIN: CN1.132 (_CIIN), U2.10
_CIOUT: CN1.101 (_CIOUT), U3.16 (B2)
_CLA: R6.2, U4.194 (~CLA)
_CLKEN: CN3.75, U2.66, U4.205 (~CLKEN)
_CPURST: CN1.109 (_CPURST), U2.9
_DMACOE: U2.103, U14.13 (_OEAB)
_DS: CN1.97 (_DS), U2.118
_DSACK0: CN1.91 (_DSACK0), U2.7
_DSACK1: CN1.1 (_DSACK1), U2.5 (I/O/GTS1)
_EMUL: CN1.31 (_EMUL), U2.2 (I/O/GTS3)
_HLT: CN1.4 (_HLT), U2.35
_INT2: CN1.82 (NC), U2.24
_INT6: CN1.43 (NC), U2.22
_IPEND: CN1.116 (_IPEND), U3.15 (B3)
_IPL0: CN1.120 (_IPL0), U2.49
_IPL1: CN1.124 (_IPL1), U2.50
_IPL2: CN1.128 (_IPL0), U2.51
_LOCK: RN21.6 (R3.2), U2.3 (I/O/GTS4), U3.3 (A1), U4.162 (~LOCK)
_LOCKE: RN21.5 (R4.2), U2.4, U4.144 (~LOCKE)
_RESET: CN1.117 (_RESET), U5.6, U5.12
_RMC: CN1.108 (_RMC), U3.17 (B1)
_SNOOP: R7.2, U2.33, U4.200 (~SNOOP)
_STERM: CN1.21 (_STERM), U2.142
_TA: CN2.58, RN22.7 (R2.2), U2.12, U4.175 (~TA)
_TBI: RN1.7 (R2.2), U2.75, U4.155 (~TBI)
_TCI: CN2.64, U2.74, U4.171 (~TCI)
_TEA: CN2.62, RN22.8 (R1.2), U2.13, U4.157 (~TEA)
_TRA: R8.2, U4.209 (~TRA)
_TS: CN2.74, FB1.1, R11.1, U2.31
nTBI_FPGA: CN3.42, U2.98
nTS_FPGA: CN3.40, U2.100

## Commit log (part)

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2026-06-24 emu: clean reboot on AMIX warm reset (skip the PISCSI-register flood)
    On `reboot`/`uadmin`, AMIX has cleared the Amiga overlay so $0-$8 maps to
    chip RAM, not the Kickstart ROM, and the emulator does not restore the
    overlay on a 68k reset. m68k_reset_newcpu's get_long(4) therefore returns
    garbage (e.g. 0xFFFFFFFF) instead of the Kickstart reset PC; the 68k then
    runs from that garbage PC, scribbling the Z3660 PISCSI registers (the
    "[!!!PISCSI] Unhandled register write" flood, thousands of lines walking
2026-06-24 sd-content: ship the AMIX firmware BOOT.BIN + document AMIX config
    Replace the SD boot-partition BOOT.BIN with a fresh amix-main HEAD build
    (12,346,484 B). HW-verified on a4000.alanara.fi: TFTP-deploys clean and boots
    'Emulation mode 4' / '68030 MMU enabled' / A3000SCSI initialised
    (UAE_030_MMU_AMIX), matching the established firmware.
    Annotate z3660cfg.txt with the AMIX options (amix_mode, service_cadence) and
    the UAE_030_MMU bootmode, and note that Kickstart/OS ROMs are user-supplied.
2026-06-24 docs: document AMIX support and correct the docker build notes
    Add docs/AMIX.md as the fork's feature + config-options reference (68030
    PMMU emulation / UAE_030_MMU, the A3000-SCSI AMIX bootstrap, amix_mode and
    service_cadence, DEMU/DSCSI debug gating, boot-mode table, AMIX requirements
    and current guest-side boot status). Add a self-contained fork section to the
    root README (quick-start / build / try-with-AMIX) linking it.
    docker/README.md: drop the obsolete 'firmware fails to compile on __packed'
2026-06-24 mmu030: backport WinUAE a333766b — PMOVE config exception no longer raises spurious F-line
    Make mmu_op30_pmove return a tri-state int (0 ok / 1 F-line / -1 MMU configuration exception only) so an invalid TC/RP decode raises only the config exception, not an additional F-line. Mirror in the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
    Found by a drift audit against WinUAE 6.0.3: the only post-4.4.0 upstream 030-MMU fix applicable to our 030-only/no-cache build. Host MMU harness 60/60; HW-verified AMIX boots to login (no behaviour 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
2026-06-25 chore: gitignore AI-agent config + investigations + bench archive (kept local)
2026-06-25 emu/diag: catch the AMIX user-PC wild-jump (BUS ERROR hunt)
    Under a fork/exec storm a freshly-exec'd AMIX user process (user base 0x80000000)
    intermittently has its PC silently corrupted to a kernel/low-region address (observed
    constant 0x080012A0), the next ifetch faults, and AMIX prints 'User BUS ERROR at <pc>,
    PC:<pc> FAULT:6'. The corruption is upstream of the fault.
    Add AMIX-gated diagnostics to m68k_run_mmu030: a 32-deep ring of retired instructions
    (start pc, opcode, next pc) plus a one-shot wild-user-PC detector that dumps the ring +
2026-06-25 emu: fix 030 MMU multi-fault continuation corrupting the bus-error frame PC
    Under demand paging, a 68030 instruction that bus-faults is resumed mid-flight by
    m68k_do_rte_mmu030 from its 030 bus-error frame: the run loop's inner retry loop
    re-runs the instruction at the PC m68k_setpci() restored from the frame. But
    mmu030_insn_start_pc was only snapshotted at the OUTER loop top, so during a
    continuation it still held the PC of the instruction that ran the RTE (the kernel's
    trap-return epilogue). If the resumed instruction faulted AGAIN -- e.g.
2026-06-25 docs(CHANGES): record the 030 PMMU multi-fault-continuation BUS ERROR fix
    Add an AMIX-fork section to CHANGES.md documenting the intermittent
    'User BUS ERROR'/panic fix (commit 7ff5774): the 030 bus-error-frame
    continuation rebuilt a re-fault's frame from a stale instruction PC, so a
    later RTE resumed the user process at a kernel PC -> wild PC. Reproduced and
    verified clean on real HW.
2026-06-25 tools: add amix-stress (030 MMU fault-path stressors + reproducers)
    Rescue the stress/reproduction tools built while hunting the AMIX 'User BUS ERROR'
    crash into tools/amix-stress/, mirroring tools/amix-bench (portable source +
    precompiled AMIX m68k binary + README + scripts):
    * amixstress.c / amixstress -- deep-recursion user-stack-growth stressor that forces
    the MOVEM -(SP) multi-fault continuation path (precompiled for AMIX 2.1c).
    * telnet_storm.py -- host-side in.telnetd storm; the ~100% reproducer.
2026-06-25 emu: gate the iack_cycle + cpureset AMIX changes on mmu_model==68030
    The two shared-path edits we made for AMIX leaked into the legacy UAE
    emulator modes (UAE_030/UAEJIT/UAE_040), so a non-AMIX AmigaOS boot no
    longer matched the pre-AMIX firmware. Confine both to the real 030 PMMU
    (currprefs.mmu_model==68030, set only for bootmode UAE_030_MMU); every
    other mode now runs the verbatim upstream code again.
    - iack_cycle: use the physical bank accessor (get_byte) to bypass the
2026-06-26 scsi: gate the 512-byte-per-sector RDB scan on amix_mode
    The per-sector RDB scan finds AMIX's root RDB at sector 2, which the upstream
    64K-stride scan never samples (it only tests the first 4 bytes of each 64K read,
    so AMIX otherwise booted the no-RDB fallback, mounted root R/W and stamped
    FSACTIVE before bcheckrc's fsck -m -> fsck-every-boot loop).
    But a plain-AmigaOS HDF can be a hybrid disk (sector-0 MBR plus an Amiga RDB at a
    sub-64K sector); the per-sector scan finds that RDB and applies geometry the
2026-06-26 emu/jit: fix -Os JIT miscompile so UAEJIT modes boot
    The AMIX BOOT.BIN-size change (47aeaf8: -O3 -> -Os + --gc-sections) miscompiles
    the hand-emitted ARM JIT codegen: entering any UAEJIT mode raised a [Core1]
    Undefined Exception at JIT-init and a [Core1] Prefetch Abort at runtime, so
    AmigaOS/UAEJIT could not boot at all (UAE_030_MMU/AMIX is non-JIT and was
    unaffected).
    Fix, keeping the rest of the firmware at -Os for BOOT.BIN size:
2026-06-27 emu: fix 030 MMU in-RTE retry-access rebuilding a mis-attributed bus-error frame
    m68k_do_rte_mmu030's "retry faulted access" re-performs the faulted access
    INSIDE the RTE. On a re-fault (a still-unmappable page) the run-loop CATCH
    rebuilt the bus-error frame from mmu030_insn_start_pc and regs.irc -- both of
    which still held THIS RTE instruction's own identity (the trap-return PC
    ~0x0800129C and opcode 0x4E73), because the inner-loop re-snapshot only runs
    after the handler returns. So a format-$B rebuild inherited the RTE's PC (a
2026-06-28 emu: raise A3000-KS auto-click cap so AMIX warm reboot clears the loader prompt
    A warm AMIX reboot (init 6) triggers a full firmware hard_reboot; on the
    re-run, the auto-click that dismisses the A3000 Kickstart "press a mouse
    button to continue" prompt was capped at 6 presses -- occasionally too few,
    wedging the boot at the loader. Raise the cap to 64 (self-limited: the press
    counter re-zeroes when the mouse-poll spin ends, so it never leaks past the
    prompt). Validated over a 24h reboot soak (13 warm reboots, all clean).
2026-06-28 emu: AMIX autoboots from SCSI id 6 alone (drop the id-6 -> drive-0 alias)
    The WD33C93 emulation hard-aliased SCSI target 6 to PISCSI backend drive 0
    (drvnum_for_target) -- a band-aid from when Amix.hdf lived only on scsi0 while
    AMIX's kernel opens root at target 6. So id 6 was only visible when the disk
    sat on scsi0; with the disk on scsi6 alone (scsi0 -1), target 6's alias probed
    the empty drive 0 -> CSR_TIMEOUT -> the Kickstart 3.1 RDB scan saw no boot
    device on id 6. A KS 3.1 RDB autoboot is ID-agnostic (it boots by RDB BootPri,
2026-06-28 docs: refresh AMIX docs -- boots to a stable login shell; SCSI-id must match install
    AMIX 2.1 now boots reliably to a stable multiuser login shell, so the docs no
    longer describe it as WIP / blocked on a guest-side race.
    - docs/AMIX.md: rewrite the status (boots to login; the post-banner stall is
    resolved by this cycle's emulator demand-paging fixes; one rare load edge
    case tracked). Fix the config example (scsi6, not scsi0) and add a prominent
    "the SCSI id must match the id AMIX was installed on (id 6 / c6d0s1)" callout;
2026-06-28 docker: containerised firmware build toolchain + fix clean-checkout build breaks
    Adds docker/ — a containerised Vitis 2023.2 / arm-none-eabi toolchain that
    builds the Z3660 firmware (and the Amiga-side drivers) reproducibly, without a
    hand-configured local Vitis install. Vitis itself is staged outside the repo
    and never committed.
    Along the way, fixes the pre-existing breaks that stop a clean, non-IDE
    (Linux/docker) build from completing:
2026-06-29 sd-content: refresh the AMIX BOOT.BIN to the current build
    Rebuilt from current amix-main — includes every fix since the 2026-06-24 binary the old copy was from (030-MMU demand-paging fix, SCSI id-6 autoboot, -Os JIT fix, warm-reset). HW-verified: cold-boots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
2026-06-29 docs: link the companion amix-kerntools repo (AMIX guest-side drivers)
    The native AMIX drivers (amix-z3660scsi, amix-z3660net) live in a separate repo, jusii/amix-kerntools. Add the link in docs/AMIX.md (the drivers row + See also) and the README fork section so users c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
2026-06-29 feat: AMIX (Amiga UNIX) support — 68030 PMMU + emulated A3000 SCSI
    Lets a Z3660 + Z-turn boot Amiga UNIX (AMIX) 2.1, which needs a real 68030
    PMMU and the A3000 mainboard SCSI controller — neither present in the stock
    firmware. Boots to a stable multiuser login shell on real hardware.
    What's added (all opt-in; per-change history in CHANGES.md):
    - 68030 PMMU emulator — new `UAE_030_MMU` bootmode, a 68030 interpreter with
    a working PMMU, ported from WinUAE 4.4.0, plus a host-side MMU test harness.

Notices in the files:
z3660-board/Z3660_kicad/Z3660_kicad9-023/Z3660_v023.kicad_pcb:
© 2026 Double H Tech
©2021 torsti76
